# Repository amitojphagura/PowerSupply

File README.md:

# Power Supply
A dual-rail bench power supply: barrel-jack DC input, switched, stepped down to two regulated outputs, 5V and ~3.3V. Designed in KiCad 9.

## Overview

Power comes in through a barrel jack, passes through a slide switch for on/off control, and feeds two independent linear regulator stages:

- An **LM7805** for a fixed **5V** rail
- An **LM317**, set via a resistor divider for an adjustable rail configured to output roughly **3.3V**

An LED indicates power status on the LM317 stage. Both rails are broken out to screw terminals and pin headers for flexible use on a bench or in another project.

## Features

- Barrel jack DC input with slide-switch power control
- **5V fixed rail** (LM7805)
- **~3.3V rail** (LM317 + R2/R3 divider, R2 = 330Ω, R3 = 560Ω)
- LED power indicator
- Output broken out via screw terminals (J5, J7) and 3-pin headers (J3, J4)
- Fully open hardware — schematic, PCB layout, and Gerbers included

## Hardware

| Component | Designator | Notes |
|---|---|---|
| Input | J6 | Barrel jack with switch contact |
| Power switch | S1 | Slide switch, in series with input |
| 5V regulator | U1 | LM7805 (TO-220) |
| Adjustable regulator | U2 | LM317 (TO-220), set for ~3.3V |
| Voltage-set resistors | R2, R3 | 330Ω / 560Ω divider on the LM317 ADJ pin |
| LED resistor | R1 | Current limit for power LED |
| Power indicator | D1 | LED |
| Input/output caps | C1, C2, C3 | Bypass/filter capacitors |
| Output terminals | J5, J7 | Screw terminals |
| Output headers | J3, J4 | 3-pin breakout headers |

## Repo Structure

```
Power Supply/
├── Power_Supply.kicad_pro       # KiCad project file
├── Power_Supply.kicad_sch       # Schematic
├── Power_Supply.kicad_pcb       # PCB layout
└── manufacturing/
    ├── Power_Supply-job.gbrjob
    ├── Power_Supply-Edge_Cuts.gbr
    ├── Power_Supply-B_Cu.gbr
    ├── Power_Supply-B_Mask.gbr
    ├── Power_Supply-B_Paste.gbr
    ├── Power_Supply-B_Silkscreen.gbr
    ├── Power_Supply-F_Cu.gbr
    ├── Power_Supply-F_Mask.gbr
    ├── Power_Supply-F_Paste.gbr
    ├── Power_Supply-F_Silkscreen.gbr
    └── drill files 
```

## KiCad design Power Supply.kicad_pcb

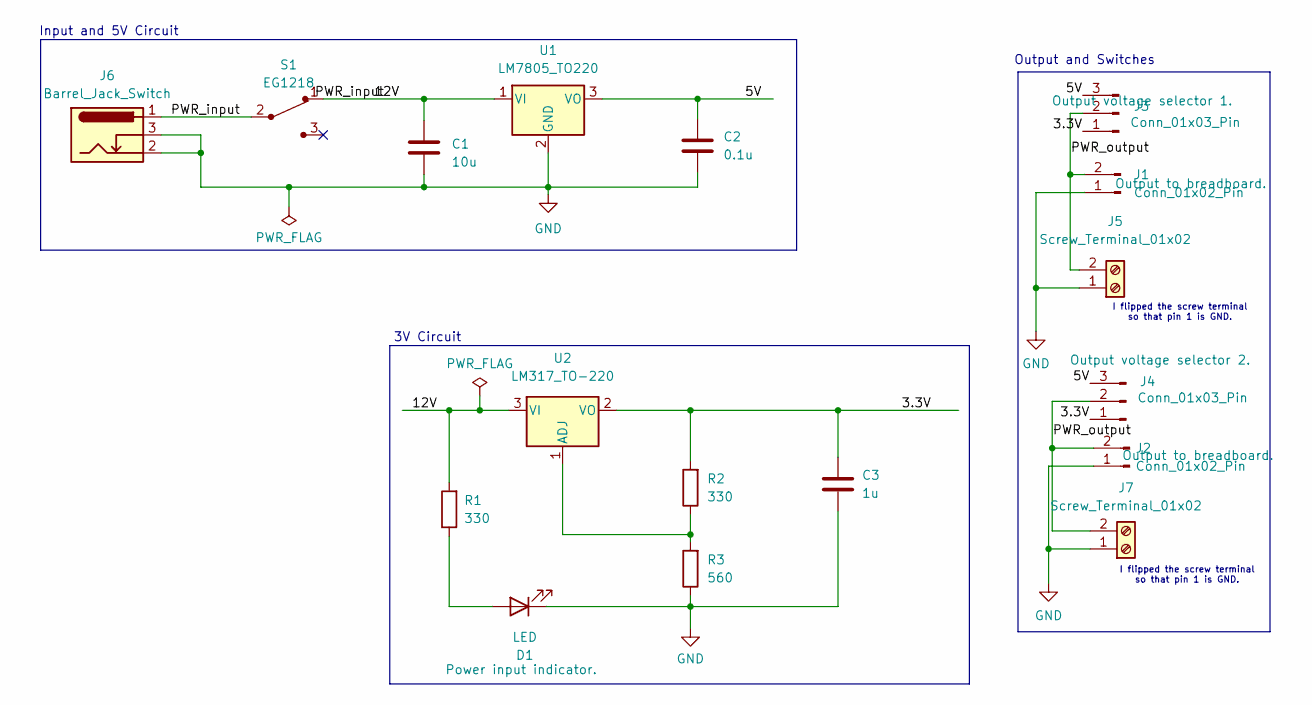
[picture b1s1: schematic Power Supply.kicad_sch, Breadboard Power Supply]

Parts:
C1: 10u; C_Disc_D3.0mm_W1.6mm_P2.50mm
C2: 0.1u; C_Disc_D3.0mm_W1.6mm_P2.50mm
C3: 1u; C_Disc_D3.0mm_W1.6mm_P2.50mm
D1: LED; LED_D5.0mm
J1, J2: Conn_01x02_Pin; PinHeader_1x02_P2.54mm_Vertical
J3, J4: Conn_01x03_Pin; PinHeader_1x03_P2.54mm_Vertical
J5, J7: Screw_Terminal_01x02; TerminalBlock_MaiXu_MX126-5.0-02P_1x02_P5.00mm
J6: Barrel_Jack_Switch; BarrelJack_Horizontal
R1, R2: 330; R_Axial_DIN0204_L3.6mm_D1.6mm_P7.62mm_Horizontal
R3: 560; R_Axial_DIN0204_L3.6mm_D1.6mm_P7.62mm_Horizontal
S1: EG1218; Switch_Slide_11.6x4mm_EG1218; MPN EG1218; Digi-Key_PN EG1903-ND
U1: LM7805_TO220; TO-220-3_Vertical
U2: LM317_TO-220; TO-220-3_Vertical

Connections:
/3.3V: C3.1, J3.1, J4.1, R2.2, U2.2 (VO)
/5V: C2.1, J3.3, J4.3, U1.3 (VO)
/12V: C1.1, R1.2, S1.1, U1.1 (VI), U2.3 (VI)
/PWR_input: J6.1, S1.2
/PWR_output: J1.2, J2.2, J3.2, J4.2, J5.2, J7.2
GND: C1.2, C2.2, C3.2, D1.1 (K), J1.1, J2.1, J5.1, J6.2, J6.3, J7.1, R3.1, U1.2 (GND)
unnamed: D1.2 (A), R1.1
unnamed: R2.1, R3.2, U2.1 (ADJ)

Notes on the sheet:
3V Circuit
Output and Switches
I flipped the screw terminal so that pin 1 is GND.
Input and 5V Circuit

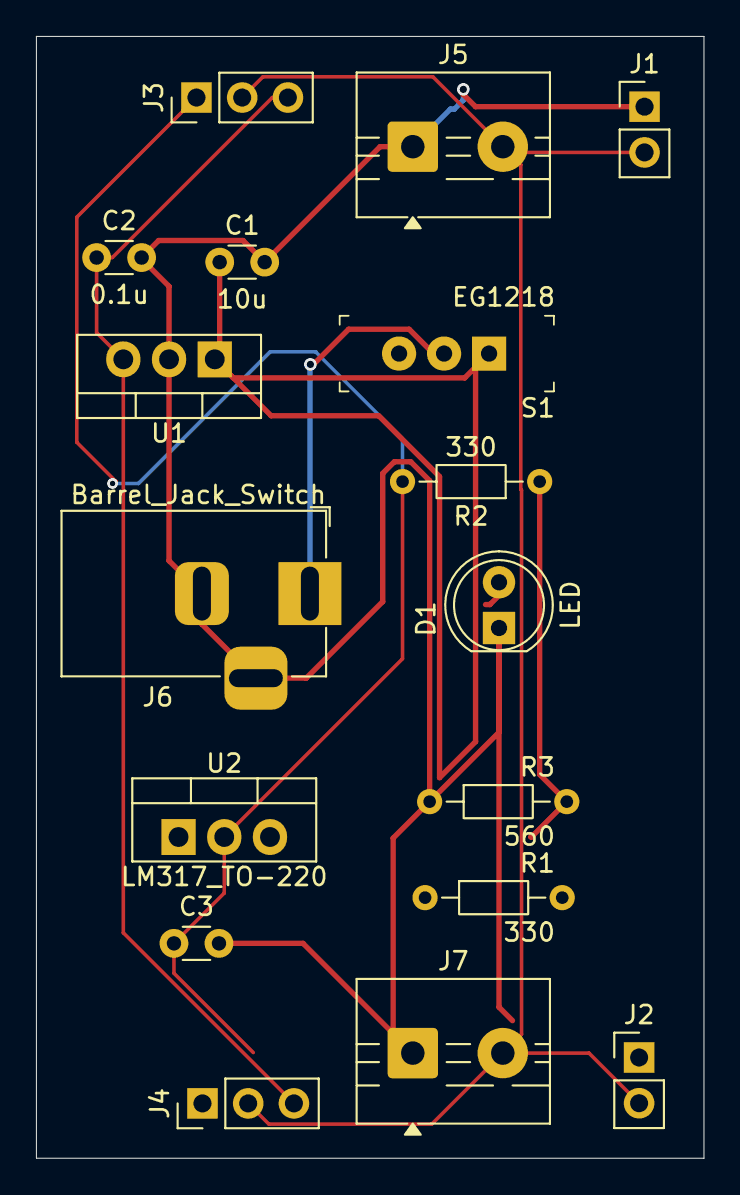
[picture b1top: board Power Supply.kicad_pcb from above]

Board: 2 copper layers, 37.1 x 62.3 mm, 17 parts (0 on the bottom side), 8 nets.
